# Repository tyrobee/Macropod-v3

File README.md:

# Macropod-v3

I made a hackboard based on the pretty well known Sayo Device.

My Hackboard has a rotary encoder for volume control, 3 keys for macros/inputs. Currently in the QMK firmware it's been coded so the left key will press W on the keyboard, the middle key will do copy, and the right key will do paste. To make this Hackboard yourself you will need all the electronics in BOM plus get the custom PCB board made, the files for that are in gerbers in the production folder. After that you will need to 3d print all 3 of the parts for the case. Next you assemble the PCB board by sautering all of the pieces together. Finally you flash the Firmware into the RP2040 micro-controller and assemble the case for the sayo device.

## Schematics

## PCB

## CAD

## BOM
| Name | Purpose | Quantity | Total Cost (USD) | Link | Distributor |
|------|--------|----------|------------------|------|------------|
| Rotary Encoder | Dial input | 1 |0 | [Buy](https://robu.in/product/rotary-encoder-module/) | Robocraze |
| RP2040 | Microcontroller | 1 | 6.38 | [Buy](https://robocraze.com/products/seeed-studio-xiao-rp2040-development-board?variant=47742255562976&country=IN&currency=INR&utm_medium=product_sync&utm_source=google&utm_content=sag_organic&utm_campaign=sag_organic&campaignid=23145906364&adgroupid=182236965810&keyword=&device=c&gad_source=1&gad_campaignid=23145906364&gbraid=0AAAAADgHQvYlPzGMG3OcYMtb-BlPsfzhf&gclid=Cj0KCQjw77bPBhC_ARIsAGAjjV_IhuaGoKQTdTU_7luZl5Y1Wit55HdLdD95t0fOEzUk7gfg4P0fwLcaAqJXEALw_wcB) | Robocraze |
| Hot-Swappable Mechanical Keyboard Switches | Keys | 1 | 9.18 | [Buy](https://stackskb.com/store/click-inc-of-linear-switch-pack-of-10/) | Stacks |
| 3d printed comps | structure | 1 | 4| [Buy]() | printing legion|
| PCB | Circuit board | 1 | 9.94| [Buy](https://jlcpcb.com/) | JLCPCB |
| USB Type-C to Type-C Cable (Zebronics) | Power & Data | 1 | 2.11 | [Buy](https://www.amazon.in/dp/B0FJ2LY2JN) | Amazon |
| Keycaps | Keys | 1 | 1.06 | [Buy](https://stackskb.com/store/numpad-keycaps/) | Stacks |

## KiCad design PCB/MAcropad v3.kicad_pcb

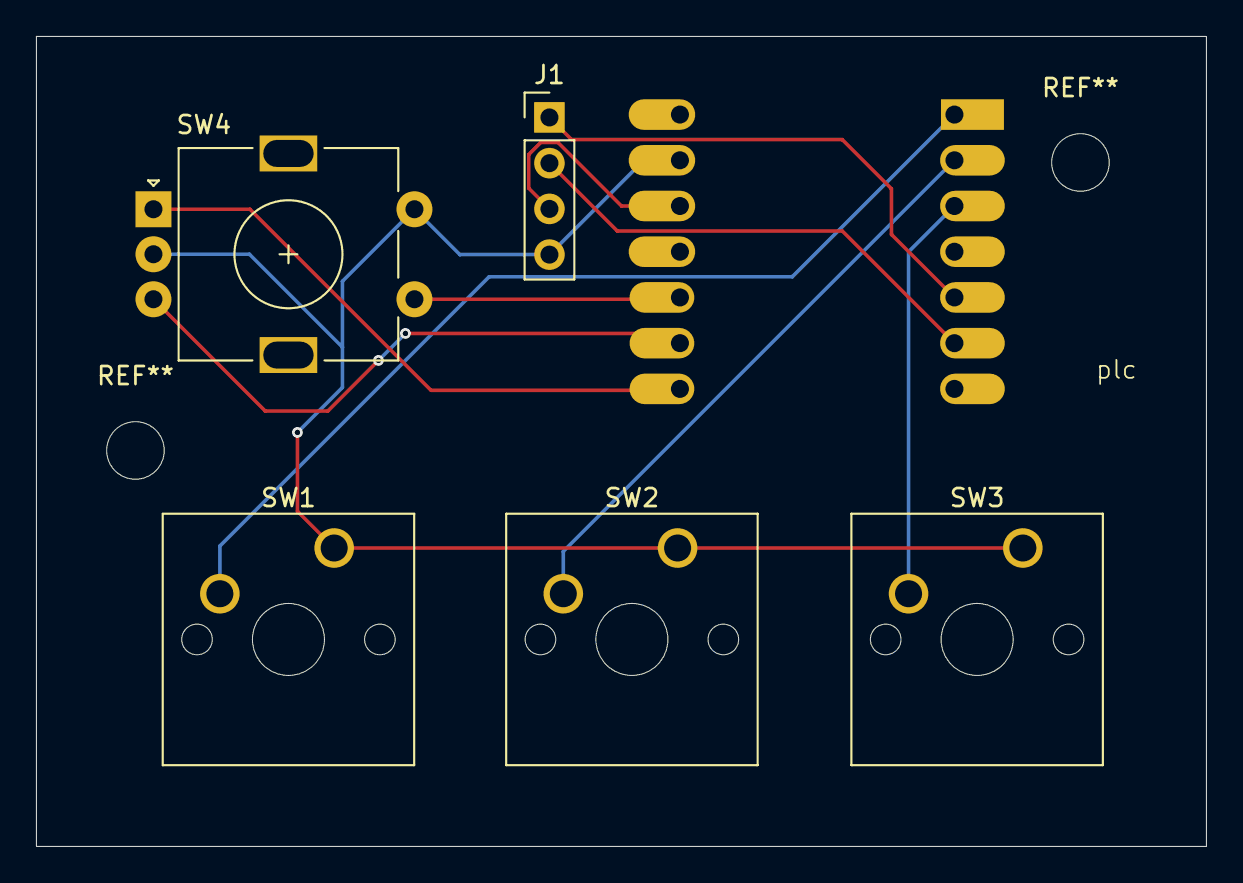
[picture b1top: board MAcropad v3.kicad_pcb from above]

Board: 2 copper layers, 65.0 x 45.0 mm, 6 parts (1 on the bottom side), 10 nets.

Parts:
J1: Conn_01x04_Socket; PinHeader_1x04_P2.54mm_Vertical
SW1, SW2, SW3: SW_Push; SW_Cherry_MX_1.00u_PCB
SW4: RotaryEncoder_Switch; RotaryEncoder_Alps_EC11E-Switch_Vertical_H20mm
U1: MOUDLE-SEEEDUINO-XIAO; XIAO-Generic-Hybrid-14P-2.54-21X17.8MM

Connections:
/SCL: J1.2, U1.6 (PA9_A5_D5_SCL)
/SDA: J1.1, U1.5 (PA8_A4_D4_SDA)
GND: J1.4, SW1.1, SW2.1, SW3.1, SW4.C, SW4.S2, U1.13 (GND)
unnamed: SW1.2, U1.1 (PA02_A0_D0)
unnamed: SW2.2, U1.2 (PA4_A1_D1)
unnamed: SW4.S1, U1.10 (PA5_A9_D9_MISO)
unnamed: SW4.B, U1.9 (PA7_A8_D8_SCK)
unnamed: SW3.2, U1.3 (PA10_A2_D2)
unnamed: SW4.A, U1.8 (PB09_A7_D7_RX)
VCC: J1.3, U1.12 (3V3)

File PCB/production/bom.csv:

Designator,Footprint,Quantity,Value,LCSC Part #
J1,PinHeader_1x04_P2.54mm_Vertical,1,Conn_01x04_Socket,
"SW1, SW2, SW3",SW_Cherry_MX_1.00u_PCB,3,SW_Push,
SW4,RotaryEncoder_Alps_EC11E-Switch_Vertical_H20mm,1,RotaryEncoder_Switch,
U1,XIAO-Generic-Hybrid-14P-2.54-21X17.8MM,1,MOUDLE-SEEEDUINO-XIAO,

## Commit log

2026-04-18 Fix image paths in README.md
    Corrected image paths in the README for schematics, PCB, and CAD sections.
2026-04-26 Revise BOM with updated links and details
    Updated links and details for RP2040 and 3D printed components.
2026-04-26 Update distributor information and add Keycaps entry
    Updated the distributor for Hot-Swappable Mechanical Keyboard Switches and added a new entry for Keycaps.
2026-04-26 Change category for '3d printed comps' in README
    Updated the category of '3d printed comps' from 'Keys' to 'structure'.
